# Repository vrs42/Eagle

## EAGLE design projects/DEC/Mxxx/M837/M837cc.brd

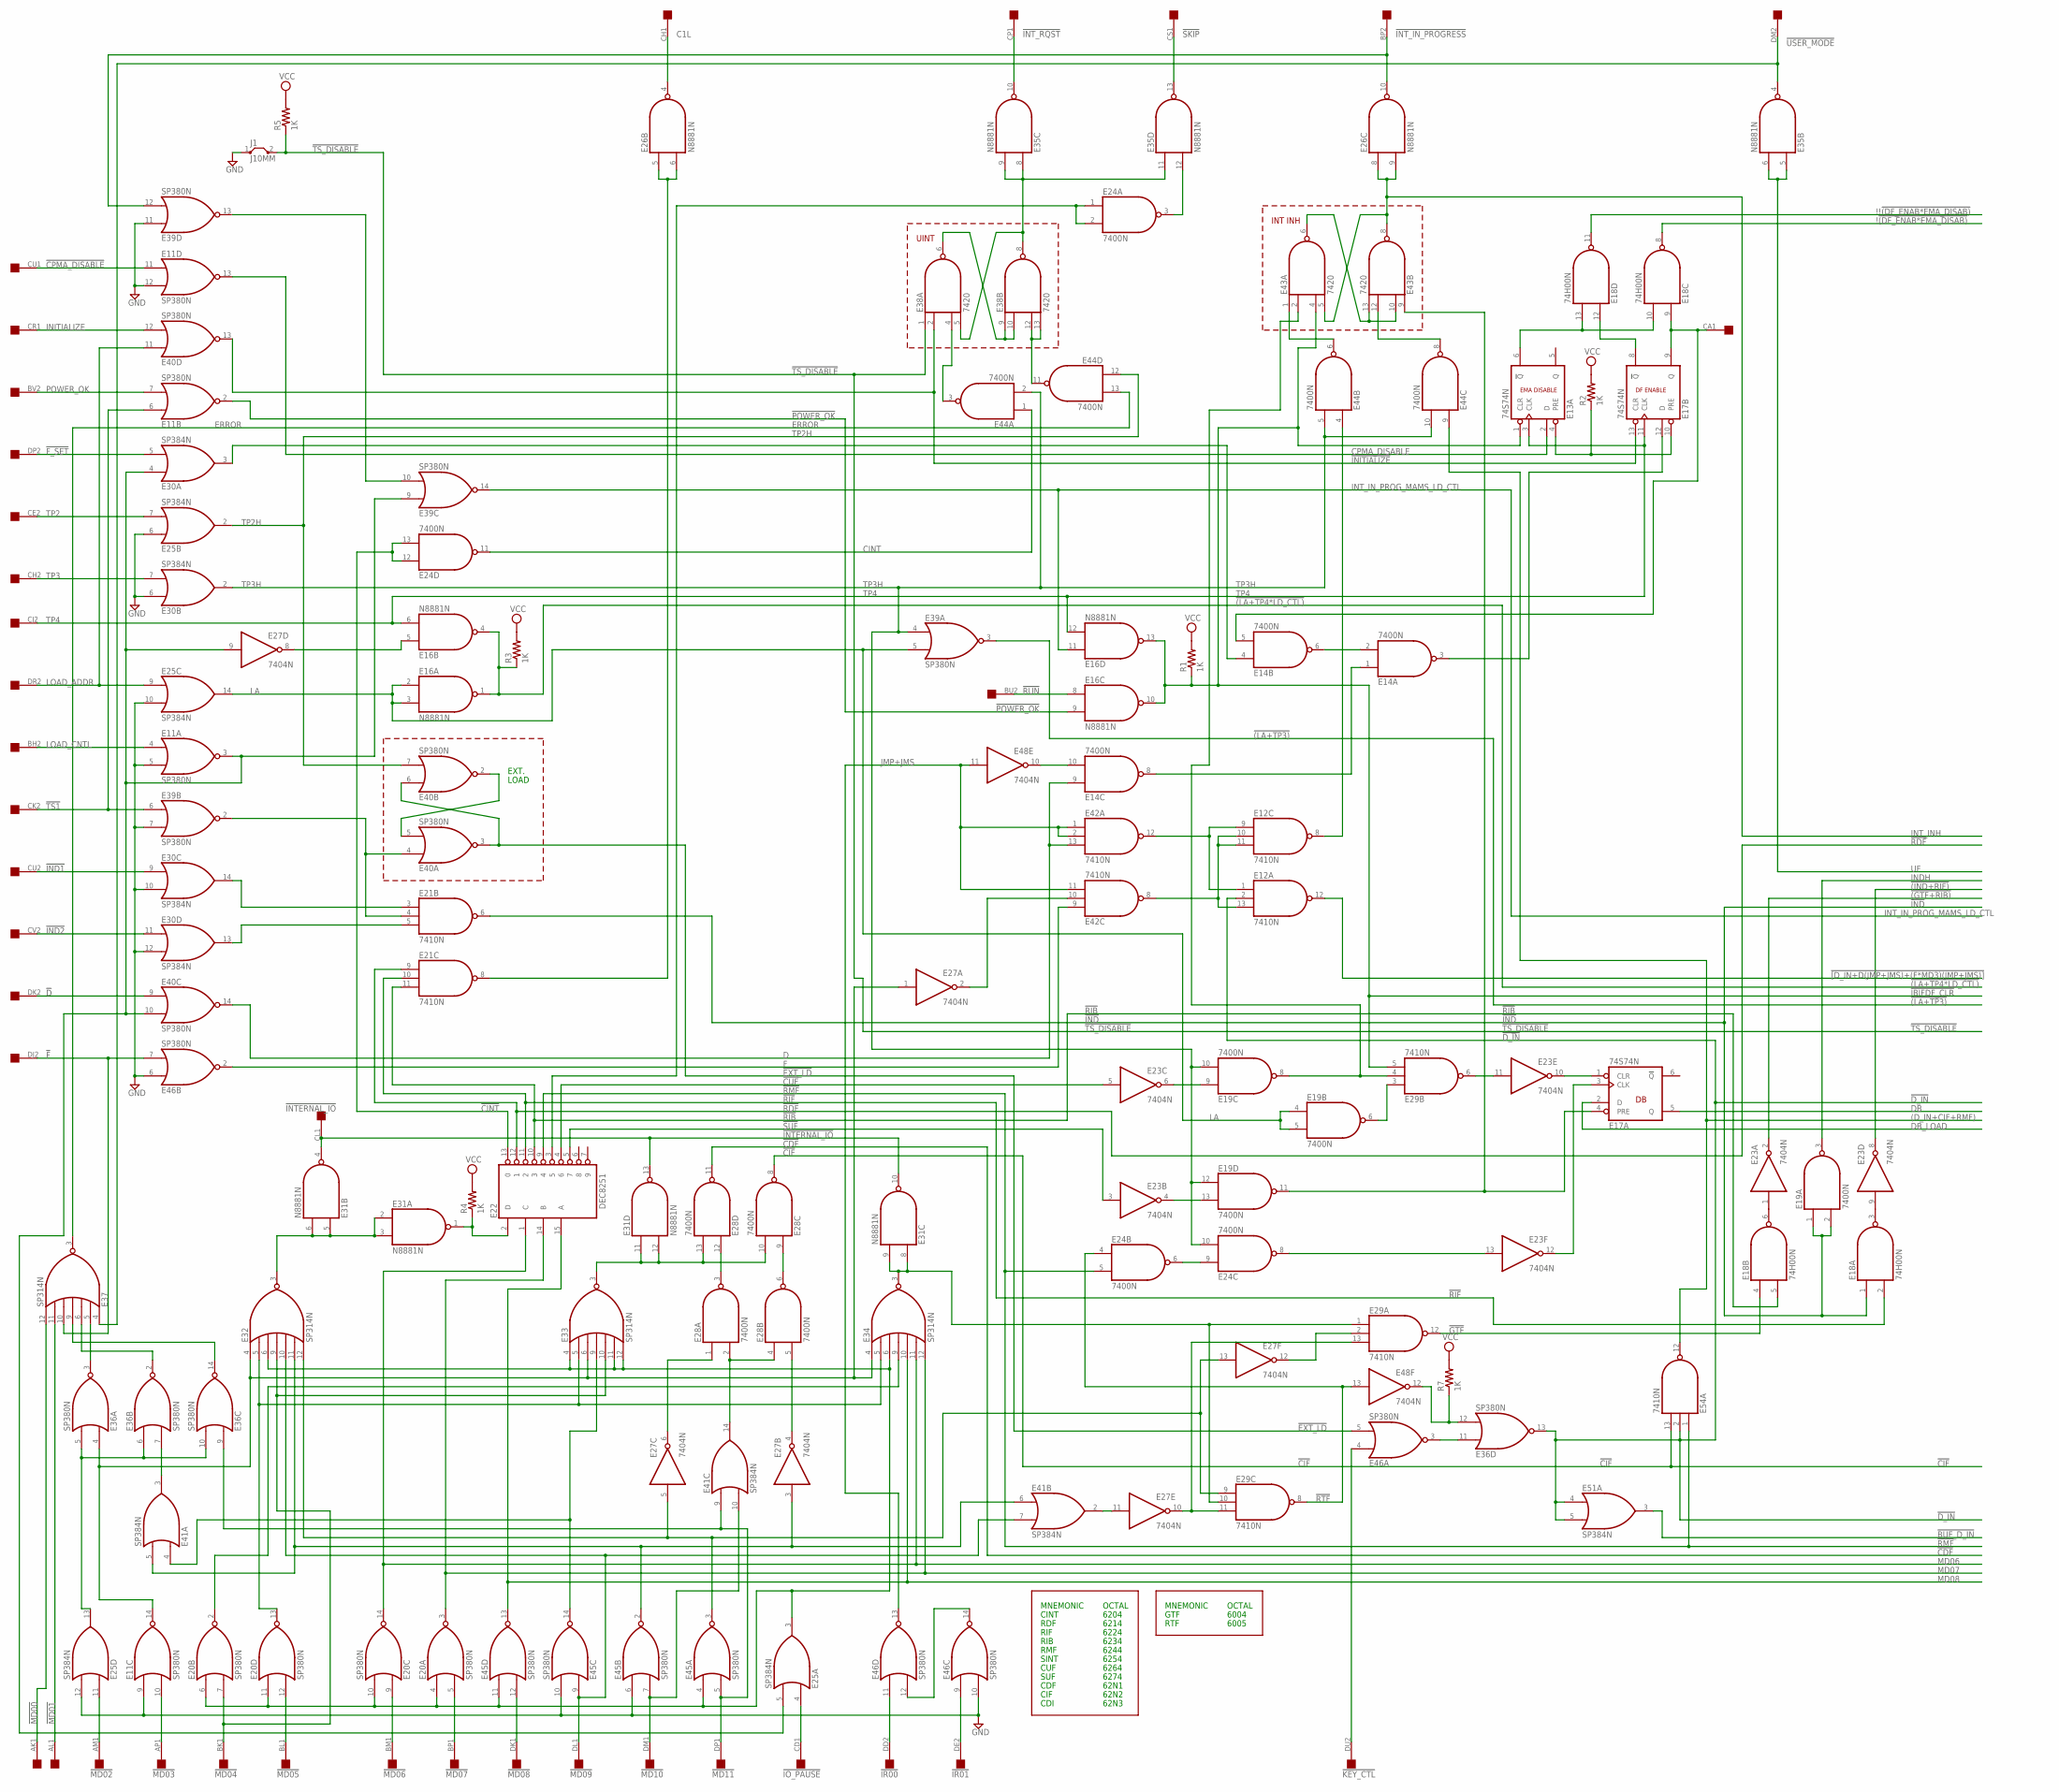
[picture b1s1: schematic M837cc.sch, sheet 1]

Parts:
E11, E20, E36, E39, E40, E45, E46: SP380N; DIL14
E12, E21, E29, E42, E54: 7410N; DIL14
E13, E17: 74S74N; DIL14
E14, E19, E24, E28, E44: 7400N; DIL14
E16, E26, E31, E35: N8881N; DIL14
E18: 74H00N; DIL14
E22: DEC8251; DIL16
E23, E27, E48: 7404N; DIL14
E25, E30, E41, E51: SP384N; DIL14
E32, E33, E34, E37: SP314N; DIL14
E38, E43: 7420; DIL14
EDGE: QUAD; EDGE-CON8
J1: J10MM; 10
R1, R2, R3, R4, R5, R7: 1K; 0207/10

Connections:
!(DF_ENAB*EMA_DISAB_L): E18.8 (O); also elsewhere on the board
!(DF_ENAB_L*EMA_DISAB_L): E18.11 (O); also elsewhere on the board
!(GTF+RIB): E23.2 (O); also elsewhere on the board
!(IND+RIF): E23.8 (O); also elsewhere on the board
!(LA+TP3): E39.3 (O); also elsewhere on the board
!(LA+TP4*LD_CTL): E16.1 (O), E16.4 (O), R3.1; also elsewhere on the board
!BMD02: E25.13 (O), E36.5 (I1), E36.6 (I0), E36.10 (I1)
!BUF_D_IN: E51.3 (O); also elsewhere on the board
!CDF: E28.11 (O); also elsewhere on the board
!CIF: E28.8 (O), E54.13 (I2); also elsewhere on the board
!CINT: E22.13 (0), E24.12 (I0), E24.13 (I1)
!CPMA_DISABLE: E11.11 (I0), EDGE.CU1
!CUF: E22.4 (6), E23.5 (I)
!D: E40.9 (I0), EDGE.DK2
!DF_ENABLE: E17.8 (!Q), E18.12 (I0)
!D_IN: E12.2 (I1), E36.13 (O), E51.4 (I0), E51.5 (I1), E54.2 (I1); also elsewhere on the board
!EMA_DISABLE: E13.6 (!Q), E18.10 (I1), E18.13 (I1)
!EXT_LD: E40.3 (O), E40.6 (I0), E46.5 (I1)
!F: E37.10 (I4), E46.7 (I1), EDGE.DJ2
!F_SET: E30.5 (I1), EDGE.DP2
!GTF: E18.4 (I0), E29.12 (O)
!IBIFDF_CLR: E13.1 (CLR), E16.10 (O), E16.13 (O), E29.5 (I2), E43.4 (I2), R1.1; also elsewhere on the board
!IND: E18.1 (I0), E19.1 (I0), E19.2 (I1), E21.6 (O); also elsewhere on the board
!IND1: E30.9 (I0), EDGE.CU2
!IND2: E30.11 (I0), EDGE.CV2
!INITIALIZE: E17.13 (CLR), E38.2 (I1), E40.13 (O)
!INTERNAL_IO: E31.4 (O), E31.10 (O), E31.13 (O), EDGE.CL1
!INT_IN_PROGRESS: E26.10 (O), E39.12 (I1), EDGE.BP2
!INT_RQST: E35.10 (O), EDGE.CP1
!IOT010XXX1XX: E22.2 (D), E31.1 (O), R4.1
!IO_PAUSE: E25.4 (I0), EDGE.CD1
!IR00: E46.11 (I0), EDGE.DD2
!IR01: E46.9 (I0), EDGE.DE2
!KEY_CTL: E46.4 (I0), EDGE.DU2
!LOAD_CNTL: E11.3 (O), E25.5 (I1), E27.9 (I), E30.4 (I0), E39.9 (I0), E40.10 (I1)
!MD00: E37.12 (I6), EDGE.AK1
!MD01: E37.11 (I5), EDGE.AL1
!MD02: E25.11 (I0), EDGE.AM1
!MD03: E11.10 (I1), EDGE.AP1
!MD04: E20.7 (I1), E32.9 (I3), E33.10 (I4), EDGE.BK1
!MD05: E20.12 (I1), EDGE.BL1
!MD06: E20.9 (I0), EDGE.BM1
!MD07: E20.5 (I1), EDGE.BP1
!MD08: E45.12 (I1), EDGE.DK1
!MD09: E32.10 (I4), E41.7 (I1), E45.9 (I0), EDGE.DL1
!MD10: E41.10 (I1), E45.7 (I1), EDGE.DM1
!MD11: E36.9 (I0), E41.9 (I0), E45.5 (I1), EDGE.DP1
!POWER_OK: E11.2 (O), E16.9 (I1)
!RDF: E21.9 (I0), E22.12 (1); also elsewhere on the board
!RIB: E18.5 (I1), E21.11 (I2), E22.10 (3)
!RIF: E18.2 (I1), E21.10 (I1), E22.11 (2)
!RMF: E22.9 (4), E24.5 (I1), E54.1 (I0); also elsewhere on the board
!RTF: E24.4 (I0), E29.8 (O), E48.13 (I)
!RUN: E16.8 (I0), EDGE.BU2
!SINT: E22.3 (5), E24.1 (I0), E24.2 (I1)
!SKIP: E35.13 (O), EDGE.CS1
!SUF: E22.5 (7), E23.3 (I)
!TS1: E11.6 (I0), E39.6 (I0), EDGE.CK2
!TS_DISABLE: E38.1 (I0), J1.2, R5.1; also elsewhere on the board
!USER_MODE: E35.4 (O), E37.4 (I0), EDGE.DM2
![D_IN+D(JMP+JMS)+(F*MD3)(JMP+JMS)]: E12.12 (O); also elsewhere on the board
(D_IN+CIF+RMF): E44.9 (I0), E54.12 (O); also elsewhere on the board
C1L: E26.4 (O), EDGE.CH1
CINT: E24.11 (O), E44.1 (I0)
CPMA_DISABLE: E11.13 (O), E13.2 (D)
D: E14.9 (I0), E40.14 (O), E42.13 (I2)
DB: E17.5 (Q); also elsewhere on the board
DB_LOAD: E17.2 (D); also elsewhere on the board
DF_ENABLE: E14.5 (I1), E17.9 (Q), E18.9 (I0), EDGE.CA1
ERROR: E37.3 (O), E44.13 (I1)
F: E42.9 (I0), E46.2 (O)
GND: E11.1 (GND), E11.5 (I1), E11.9 (I0), E11.12 (I1), E12.7 (GND), E13.7 (GND), E14.7 (GND), E16.7 (GND), E17.7 (GND), E18.7 (GND), E19.7 (GND), E20.1 (GND), E21.7 (GND), E22.8 (GND), E23.7 (GND), E24.7 (GND), E25.1 (GND), E25.6 (I0), E25.10 (I1), E25.12 (I1), E26.7 (GND), E27.7 (GND), E28.7 (GND), E29.7 (GND), E30.1 (GND), E30.6 (I0), E30.10 (I1), E30.12 (I1), E31.7 (GND), E32.1 (GND), E33.1 (GND), E34.1 (GND), E35.7 (GND), E36.1 (GND), E37.1 (GND), E38.7 (GND), E39.1 (GND), E39.7 (I1), E39.11 (I0), E40.1 (GND), E41.1 (GND), E42.7 (GND), E43.7 (GND), E44.7 (GND), E45.1 (GND), E45.6 (I0), E45.10 (I1), E46.1 (GND), E46.6 (I0), E46.10 (I1), E48.7 (GND), E51.1 (GND), E54.7 (GND), J1.1; also elsewhere on the board
IND1L: E21.3 (I0), E30.14 (O)
IND2L: E21.5 (I2), E30.13 (O)
INDH: E19.3 (O); also elsewhere on the board
INITIALIZE: E40.12 (I1), EDGE.CR1
INT_INH: E26.8 (I0), E26.9 (I1), E43.5 (I3), E43.8 (O); also elsewhere on the board
INT_IN_PROGRESS: E39.10 (I1), E39.13 (O)
INT_IN_PROG_MAMS_LD_CTL: E16.11 (I0), E39.14 (O); also elsewhere on the board
IOT000000XXX: E29.1 (I0), E29.10 (I1), E31.8 (I0), E31.9 (I1), E34.3 (O)
IOT010XXX0XX: E28.10 (I1), E28.13 (I1), E31.11 (I0), E31.12 (I1), E33.3 (O)
IOT010XXX1XX: E31.2 (I0), E31.3 (I1), E31.5 (I0), E31.6 (I1), E32.3 (O)
IO_PAUSE: E20.4 (I0), E20.6 (I0), E20.10 (I1), E20.11 (I0), E25.3 (O), E32.6 (I2), E33.4 (I0), E33.11 (I5), E33.12 (I6), E34.6 (I2), E45.4 (I0), E45.11 (I0)
IR01: E46.12 (I1), E46.14 (O)
JMP+JMS: E42.1 (I0), E42.2 (I1), E42.11 (I2), E46.13 (O), E48.11 (I)
LA: E16.2 (I0), E16.3 (I1), E19.4 (I0), E19.5 (I1), E25.14 (O), E39.5 (I1)
LOAD_ADDR: E25.9 (I0), E40.11 (I0), EDGE.DR2
LOAD_CNTL: E11.4 (I0), EDGE.BH2
LOAD_CNTLH: E16.5 (I0), E27.8 (O)
MD03: E11.14 (O), E27.1 (I), E32.4 (I0), E33.6 (I2), E34.4 (I0), E36.4 (I0)
MD03L: E27.2 (O), E42.10 (I1)
MD04: E20.2 (O), E34.9 (I3)
MD05: E20.13 (O), E32.5 (I1), E33.5 (I1), E34.5 (I1)
MD06: E20.14 (O), E22.1 (C), E34.11 (I5); also elsewhere on the board
MD07: E20.3 (O), E22.14 (B), E34.12 (I6); also elsewhere on the board
MD08: E22.15 (A), E34.10 (I4), E45.13 (O); also elsewhere on the board
MD09: E33.9 (I3), E41.4 (I0), E45.14 (O)
MD10: E27.3 (I), E32.11 (I5), E41.5 (I1), E41.6 (I0), E45.2 (O)
MD11: E27.5 (I), E27.13 (I), E29.9 (I0), E32.12 (I6), E45.3 (O)
MYC1: E21.8 (O), E26.5 (I0), E26.6 (I1)
unnamed: E24.3 (O), E35.12 (I1)
unnamed: E27.10 (O), E29.11 (I2), E29.13 (I2)
unnamed: E36.3 (O), E37.5 (I1)
unnamed: E36.2 (O), E37.6 (I2)
unnamed: E36.14 (O), E37.9 (I3)
unnamed: E14.2 (I1), E14.6 (O)
unnamed: E38.4 (I2), E44.3 (O)
unnamed: E40.2 (O), E40.5 (I1)
unnamed: E27.11 (I), E41.2 (O)
unnamed: E38.12 (I2), E38.13 (I3), E44.11 (O)
unnamed: E38.6 (O), E38.9 (I0), E38.10 (I1)
unnamed: E23.13 (I), E24.8 (O)
unnamed: E43.6 (O), E43.10 (I1), E43.13 (I3)
unnamed: E14.1 (I0), E14.8 (O)
unnamed: E36.7 (I1), E41.3 (O)
unnamed: E17.3 (CLK), E23.12 (O)
unnamed: E14.10 (I1), E48.10 (O)
unnamed: E18.3 (O), E23.9 (I)
unnamed: E12.10 (I1), E12.11 (I2), E12.13 (I2), E42.8 (O)
unnamed: E13.4 (PRE), E17.10 (PRE), R2.1
unnamed: E14.4 (I0), E30.3 (O)
unnamed: E12.1 (I0), E12.9 (I0), E42.12 (O)
unnamed: E18.6 (O), E23.1 (I)
unnamed: E14.3 (O), E17.12 (D)
unnamed: E28.2 (I1), E28.4 (I0), E41.14 (O)
unnamed: E19.6 (O), E29.3 (I0)
unnamed: E19.8 (O), E29.4 (I1), E43.2 (I1)
unnamed: E28.3 (O), E28.12 (I0)
unnamed: E28.6 (O), E28.9 (I0)
unnamed: E27.6 (O), E28.1 (I0)
unnamed: E27.4 (O), E28.5 (I1)
unnamed: E24.6 (O), E24.9 (I0)
unnamed: E19.13 (I1), E23.4 (O)
unnamed: E19.9 (I0), E23.6 (O)
unnamed: E17.1 (CLR), E23.10 (O)
unnamed: E23.11 (I), E29.6 (O)
unnamed: E27.12 (O), E29.2 (I1)
unnamed: E36.11 (I0), E46.3 (O)
unnamed: E17.4 (PRE), E19.11 (O), E43.9 (I0)
unnamed: E12.8 (O), E44.4 (I0)
unnamed: E43.1 (I0), E44.6 (O)
unnamed: E43.12 (I2), E44.8 (O)
POWER_OK: E11.7 (I1), EDGE.BV2
RTF: E36.12 (I1), E48.12 (O), R7.1
TP2: E25.7 (I1), EDGE.CE2
TP2H: E25.2 (O), E40.7 (I1), E44.12 (I0)
TP3: E30.7 (I1), EDGE.CH2
TP3H: E19.10 (I1), E19.12 (I0), E24.10 (I1), E30.2 (O), E39.4 (I0), E44.2 (I1), E44.5 (I1), E44.10 (I1)
TP4: E13.3 (CLK), E16.6 (I1), E16.12 (I1), E17.11 (CLK), EDGE.CJ2
TS1: E21.4 (I1), E39.2 (O), E40.4 (I0)
UF: E35.5 (I0), E35.6 (I1); also elsewhere on the board
UINT: E35.8 (I0), E35.9 (I1), E35.11 (I0), E38.5 (I3), E38.8 (O)
VCC: E11.8 (VCC), E12.14 (VCC), E13.14 (VCC), E14.14 (VCC), E16.14 (VCC), E17.14 (VCC), E18.14 (VCC), E19.14 (VCC), E20.8 (VCC), E21.14 (VCC), E22.16 (VCC), E23.14 (VCC), E24.14 (VCC), E25.8 (VCC), E26.14 (VCC), E27.14 (VCC), E28.14 (VCC), E29.14 (VCC), E30.8 (VCC), E31.14 (VCC), E32.8 (VCC), E33.8 (VCC), E34.8 (VCC), E35.14 (VCC), E36.8 (VCC), E37.8 (VCC), E38.14 (VCC), E39.8 (VCC), E40.8 (VCC), E41.8 (VCC), E42.14 (VCC), E43.14 (VCC), E44.14 (VCC), E45.8 (VCC), E46.8 (VCC), E48.14 (VCC), E51.8 (VCC), E54.14 (VCC), R1.2, R2.2, R3.2, R4.2, R5.2, R7.2; also elsewhere on the board

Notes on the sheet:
OCTAL
MNEMONIC
CINT
RDF
RIF
RIB
RMF
SINT
CUF
SUF
CDF
CIF
CDI
6204
6214
6224
6234
6244
6254
6264
6274
62N1
62N2
62N3
GTF
RTF
6004
6005
EXT.
LOAD
UINT
INT INH
EMA DISABLE
DF ENABLE

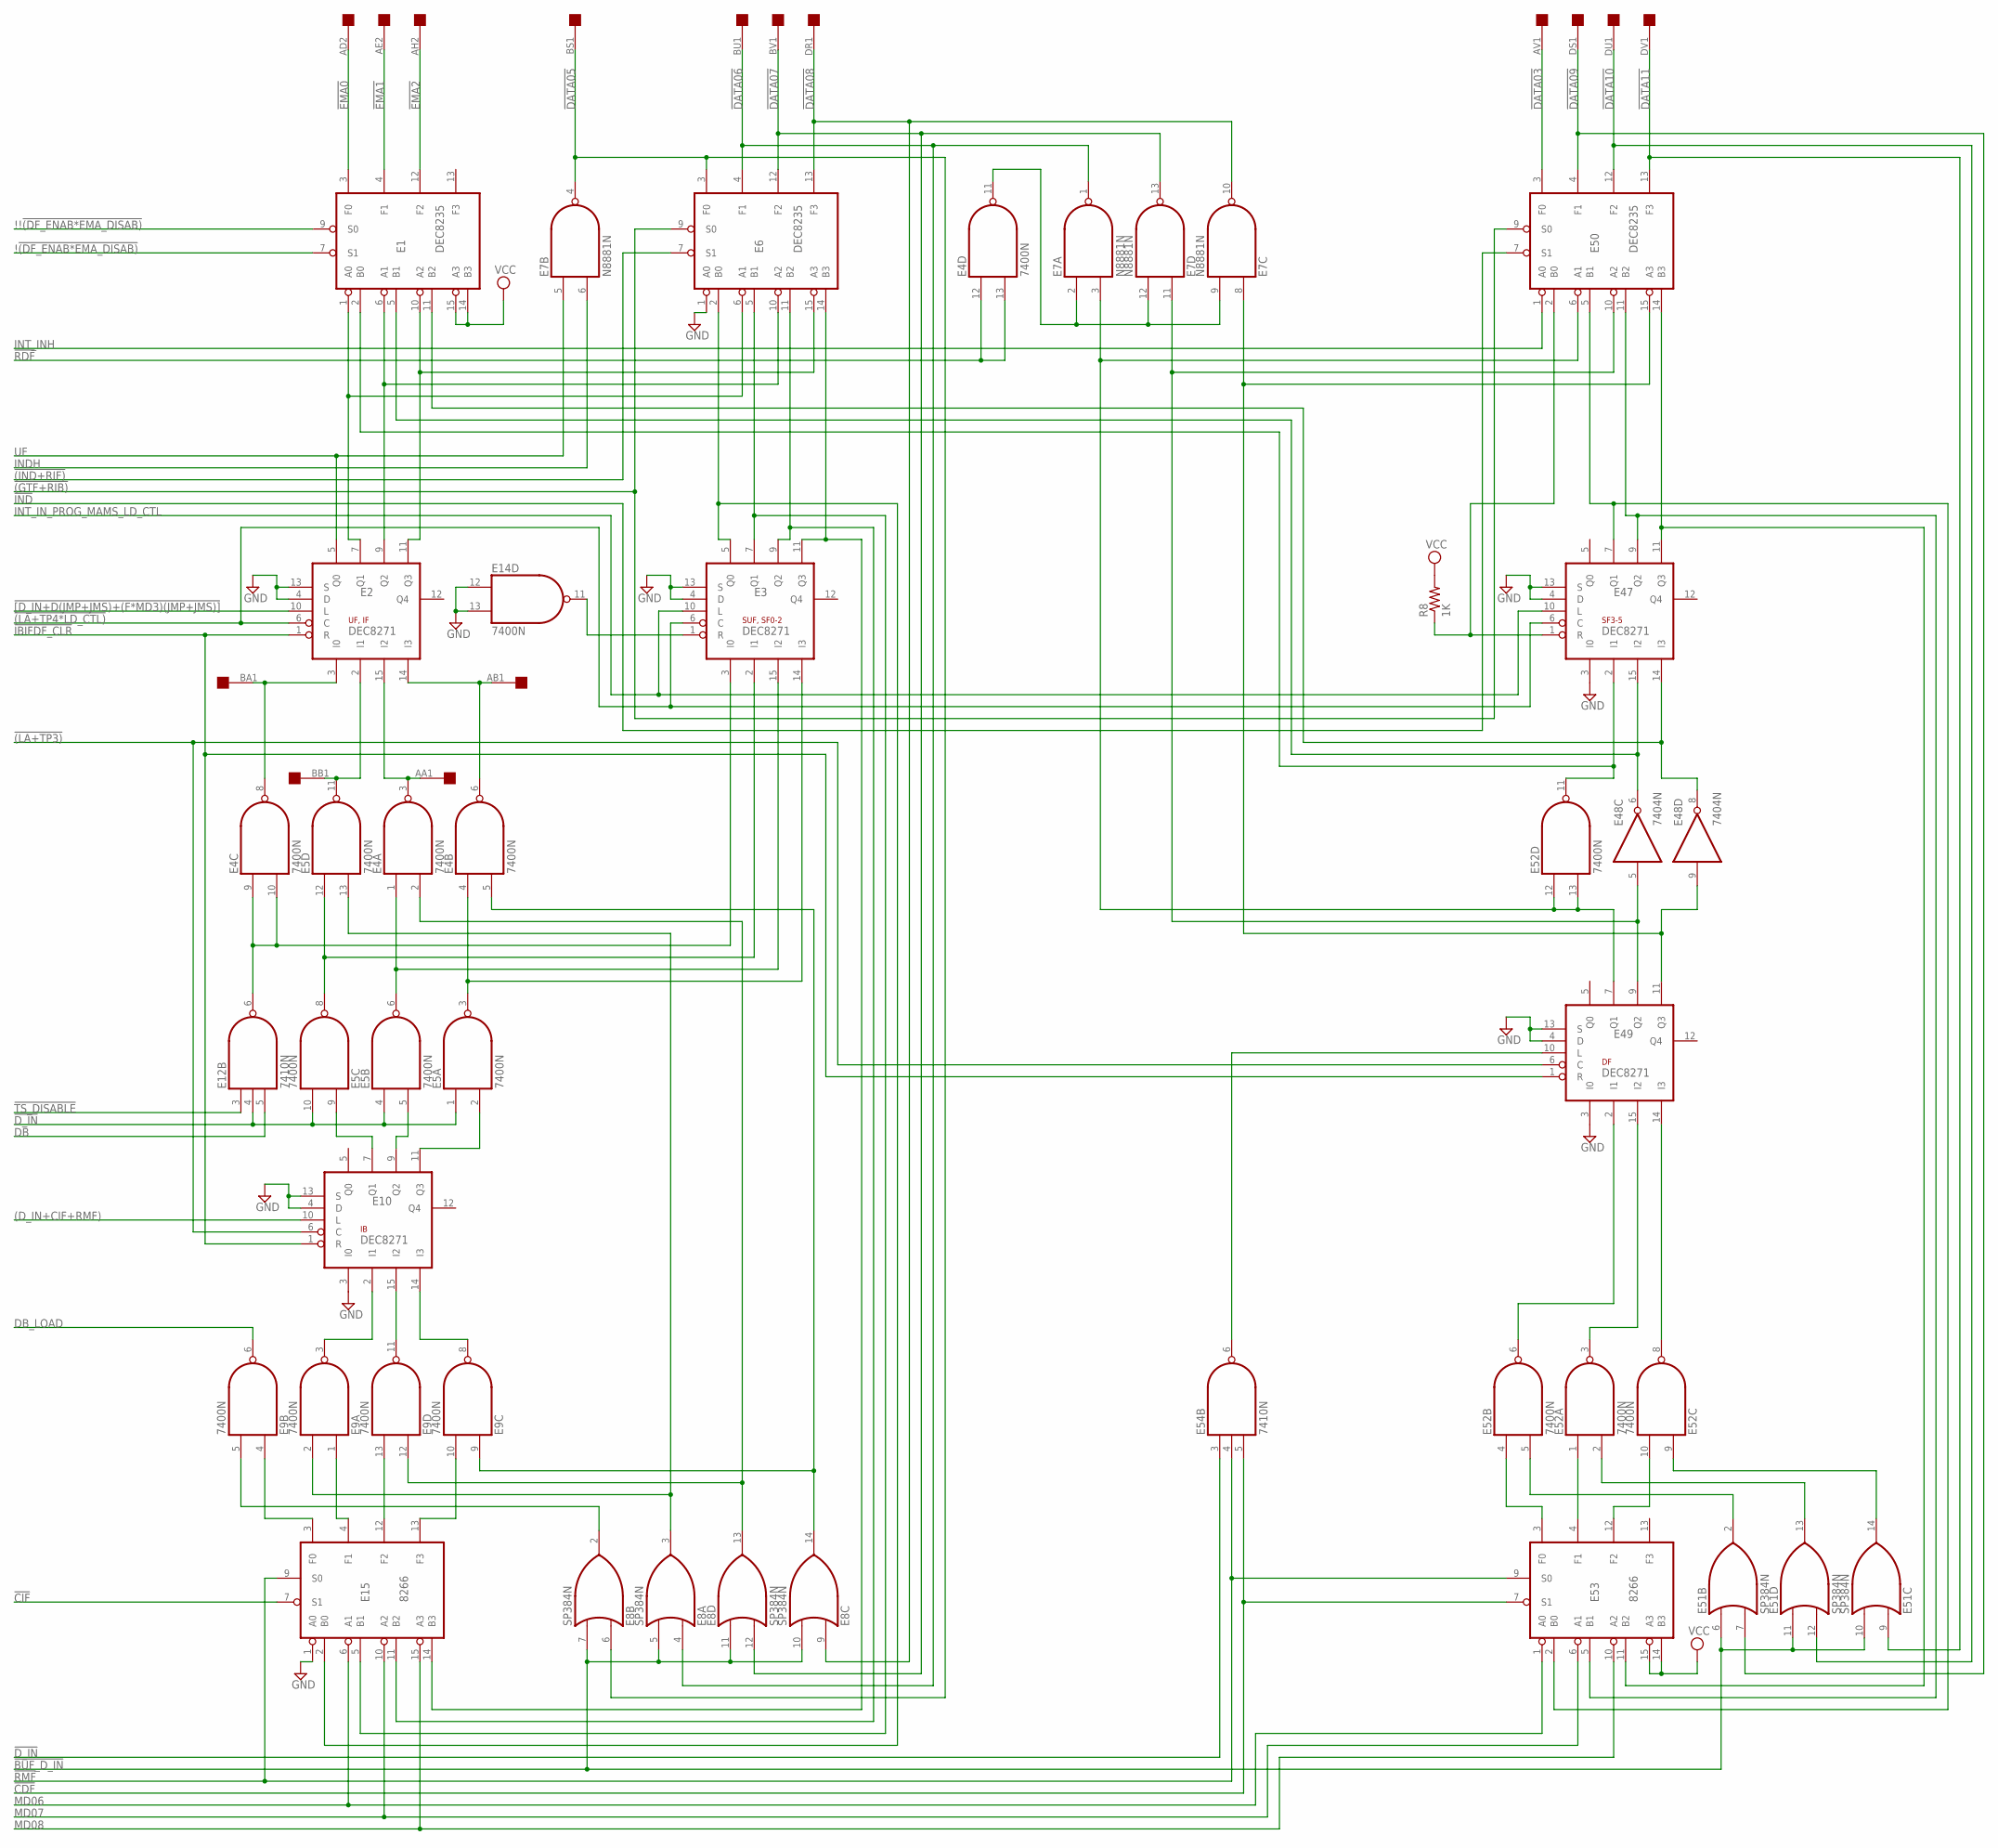
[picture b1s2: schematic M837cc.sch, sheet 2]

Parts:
E1, E6, E50: DEC8235; DIL16
E2, E3, E10, E47, E49: DEC8271; DIL16
E4, E5, E9, E14, E52: 7400N; DIL14
E7: N8881N; DIL14
E8, E51: SP384N; DIL14
E12, E54: 7410N; DIL14
E15, E53: 8266; DIL16
E48: 7404N; DIL14
EDGE: QUAD; EDGE-CON8
R8: 1K; 0207/10

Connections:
!(DF_ENAB*EMA_DISAB_L): E1.7 (S1); also elsewhere on the board
!(DF_ENAB_L*EMA_DISAB_L): E1.9 (S0); also elsewhere on the board
!(GTF+RIB): E6.9 (S0), E50.9 (S0); also elsewhere on the board
!(IND+RIF): E6.7 (S1); also elsewhere on the board
!(LA+TP3): E10.6 (C), E49.6 (C); also elsewhere on the board
!(LA+TP4*LD_CTL): E2.6 (C), E3.6 (C), E47.6 (C); also elsewhere on the board
!BUF_D_IN: E8.5 (I1), E8.7 (I1), E8.10 (I1), E8.11 (I0), E51.6 (I0), E51.10 (I1), E51.11 (I0); also elsewhere on the board
!CDF: E53.7 (S1), E54.5 (I2); also elsewhere on the board
!CIF: E15.7 (S1); also elsewhere on the board
!DATA03: E50.3 (F0), EDGE.AV1
!DATA05: E6.3 (F0), E7.4 (O), E8.6 (I0), EDGE.BS1
!DATA06: E6.4 (F1), E7.1 (O), E8.4 (I0), EDGE.BU1
!DATA07: E6.12 (F2), E7.13 (O), E8.12 (I1), EDGE.BV1
!DATA08: E6.13 (F3), E7.10 (O), E8.9 (I0), EDGE.DR1
!DATA09: E50.4 (F1), E51.7 (I1), EDGE.DS1
!DATA10: E50.12 (F2), E51.12 (I1), EDGE.DU1
!DATA11: E50.13 (F3), E51.9 (I0), EDGE.DV1
!D_IN: E5.1 (I0), E5.4 (I0), E5.10 (I1), E12.4 (I1), E54.3 (I0); also elsewhere on the board
!EMA0: E1.3 (F0), EDGE.AD2
!EMA1: E1.4 (F1), EDGE.AE2
!EMA2: E1.12 (F2), EDGE.AH2
!IBIFDF_CLR: E2.1 (R), E10.1 (R), E49.1 (R); also elsewhere on the board
!IND: E50.7 (S1); also elsewhere on the board
!RDF: E4.12 (I0), E4.13 (I1); also elsewhere on the board
!RMF: E15.9 (S0), E53.9 (S0), E54.4 (I1); also elsewhere on the board
!TS_DISABLE: E12.3 (I0); also elsewhere on the board
![D_IN+D(JMP+JMS)+(F*MD3)(JMP+JMS)]: E2.10 (L); also elsewhere on the board
(D_IN+CIF+RMF): E10.10 (L); also elsewhere on the board
DB: E12.5 (I2); also elsewhere on the board
DB_LOAD: E9.6 (O); also elsewhere on the board
DF0: E7.3 (I1), E49.7 (Q1), E50.6 (A1), E52.12 (I0), E52.13 (I1)
DF1: E7.11 (I0), E48.5 (I), E49.9 (Q2), E50.10 (A2)
DF2: E7.8 (I0), E48.9 (I), E49.11 (Q3), E50.15 (A3)
GND: E1.8 (GND), E2.4 (D), E2.8 (GND), E2.13 (S), E3.4 (D), E3.8 (GND), E3.13 (S), E4.7 (GND), E5.7 (GND), E6.1 (A0), E6.8 (GND), E7.7 (GND), E8.1 (GND), E9.7 (GND), E10.3 (I0), E10.4 (D), E10.8 (GND), E10.13 (S), E12.7 (GND), E14.7 (GND), E14.12 (I0), E14.13 (I1), E15.1 (A0), E15.8 (GND), E47.3 (I0), E47.4 (D), E47.8 (GND), E47.13 (S), E48.7 (GND), E49.3 (I0), E49.4 (D), E49.8 (GND), E49.13 (S), E50.8 (GND), E51.1 (GND), E52.7 (GND), E53.8 (GND), E54.7 (GND); also elsewhere on the board
IB0: E5.9 (I0), E10.7 (Q1)
IB1: E5.5 (I1), E10.9 (Q2)
IB2: E5.2 (I1), E10.11 (Q3)
IF0: E1.1 (A0), E2.7 (Q1), E6.6 (A1)
IF1: E1.6 (A1), E2.9 (Q2), E6.10 (A2)
IF2: E1.10 (A2), E2.11 (Q3), E6.15 (A3)
INDH: E7.6 (I1); also elsewhere on the board
INT_INH: E50.1 (A0); also elsewhere on the board
INT_IN_PROG_MAMS_LD_CTL: E3.10 (L), E47.10 (L); also elsewhere on the board
MD06: E15.6 (A1), E53.1 (A0); also elsewhere on the board
MD07: E15.10 (A2), E53.6 (A1); also elsewhere on the board
MD08: E15.15 (A3), E53.10 (A2); also elsewhere on the board
unnamed: E9.4 (I0), E15.3 (F0)
unnamed: E9.1 (I0), E15.4 (F1)
unnamed: E9.13 (I1), E15.12 (F2)
unnamed: E9.10 (I1), E15.13 (F3)
unnamed: E8.2 (O), E9.5 (I1)
unnamed: E5.13 (I1), E8.3 (O), E9.2 (I1)
unnamed: E4.2 (I1), E8.13 (O), E9.12 (I0)
unnamed: E4.5 (I1), E8.14 (O), E9.9 (I0)
unnamed: E9.11 (O), E10.15 (I2)
unnamed: E9.3 (O), E10.2 (I1)
unnamed: E9.8 (O), E10.14 (I3)
unnamed: E3.14 (I3), E4.4 (I0), E5.3 (O)
unnamed: E3.15 (I2), E4.1 (I0), E5.6 (O)
unnamed: E3.2 (I1), E5.8 (O), E5.12 (I0)
unnamed: E3.3 (I0), E4.9 (I0), E4.10 (I1), E12.6 (O)
unnamed: E1.11 (B2), E47.14 (I3), E48.8 (O)
unnamed: E1.5 (B1), E47.15 (I2), E48.6 (O)
unnamed: E1.2 (B0), E47.2 (I1), E52.11 (O)
unnamed: E49.10 (L), E54.6 (O)
unnamed: E51.2 (O), E52.5 (I1)
unnamed: E51.13 (O), E52.2 (I1)
unnamed: E51.14 (O), E52.9 (I0)
unnamed: E52.1 (I0), E53.4 (F1)
unnamed: E52.10 (I1), E53.12 (F2)
unnamed: E3.1 (R), E14.11 (O)
unnamed: E52.4 (I0), E53.3 (F0)
unnamed: E49.14 (I3), E52.8 (O)
unnamed: E49.15 (I2), E52.3 (O)
unnamed: E49.2 (I1), E52.6 (O)
unnamed: E47.1 (R), E50.2 (B0), R8.1
RDF: E4.11 (O), E7.2 (I0), E7.9 (I1), E7.12 (I1)
SF0_L: E3.7 (Q1), E6.5 (B1), E15.5 (B1)
SF1_L: E3.9 (Q2), E6.11 (B2), E15.11 (B2)
SF2_L: E3.11 (Q3), E6.14 (B3), E15.14 (B3)
SF3_L: E47.7 (Q1), E50.5 (B1), E53.2 (B0)
SF4_L: E47.9 (Q2), E50.11 (B2), E53.5 (B1)
SF5_L: E47.11 (Q3), E50.14 (B3), E53.11 (B2)
SUF_L: E3.5 (Q0), E6.2 (B0), E15.2 (B0)
TP_AA1: E2.15 (I2), E4.3 (O), EDGE.AA1
TP_AB1: E2.14 (I3), E4.6 (O), EDGE.AB1
TP_BA1: E2.3 (I0), E4.8 (O), EDGE.BA1
TP_BB1: E2.2 (I1), E5.11 (O), EDGE.BB1
UF: E2.5 (Q0), E7.5 (I0); also elsewhere on the board
VCC: E1.14 (B3), E1.15 (A3), E1.16 (VCC), E2.16 (VCC), E3.16 (VCC), E4.14 (VCC), E5.14 (VCC), E6.16 (VCC), E7.14 (VCC), E8.8 (VCC), E9.14 (VCC), E10.16 (VCC), E12.14 (VCC), E14.14 (VCC), E15.16 (VCC), E47.16 (VCC), E48.14 (VCC), E49.16 (VCC), E50.16 (VCC), E51.8 (VCC), E52.14 (VCC), E53.14 (B3), E53.15 (A3), E53.16 (VCC), E54.14 (VCC), R8.2; also elsewhere on the board

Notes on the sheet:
SUF, SF0-2
UF, IF
SF3-5

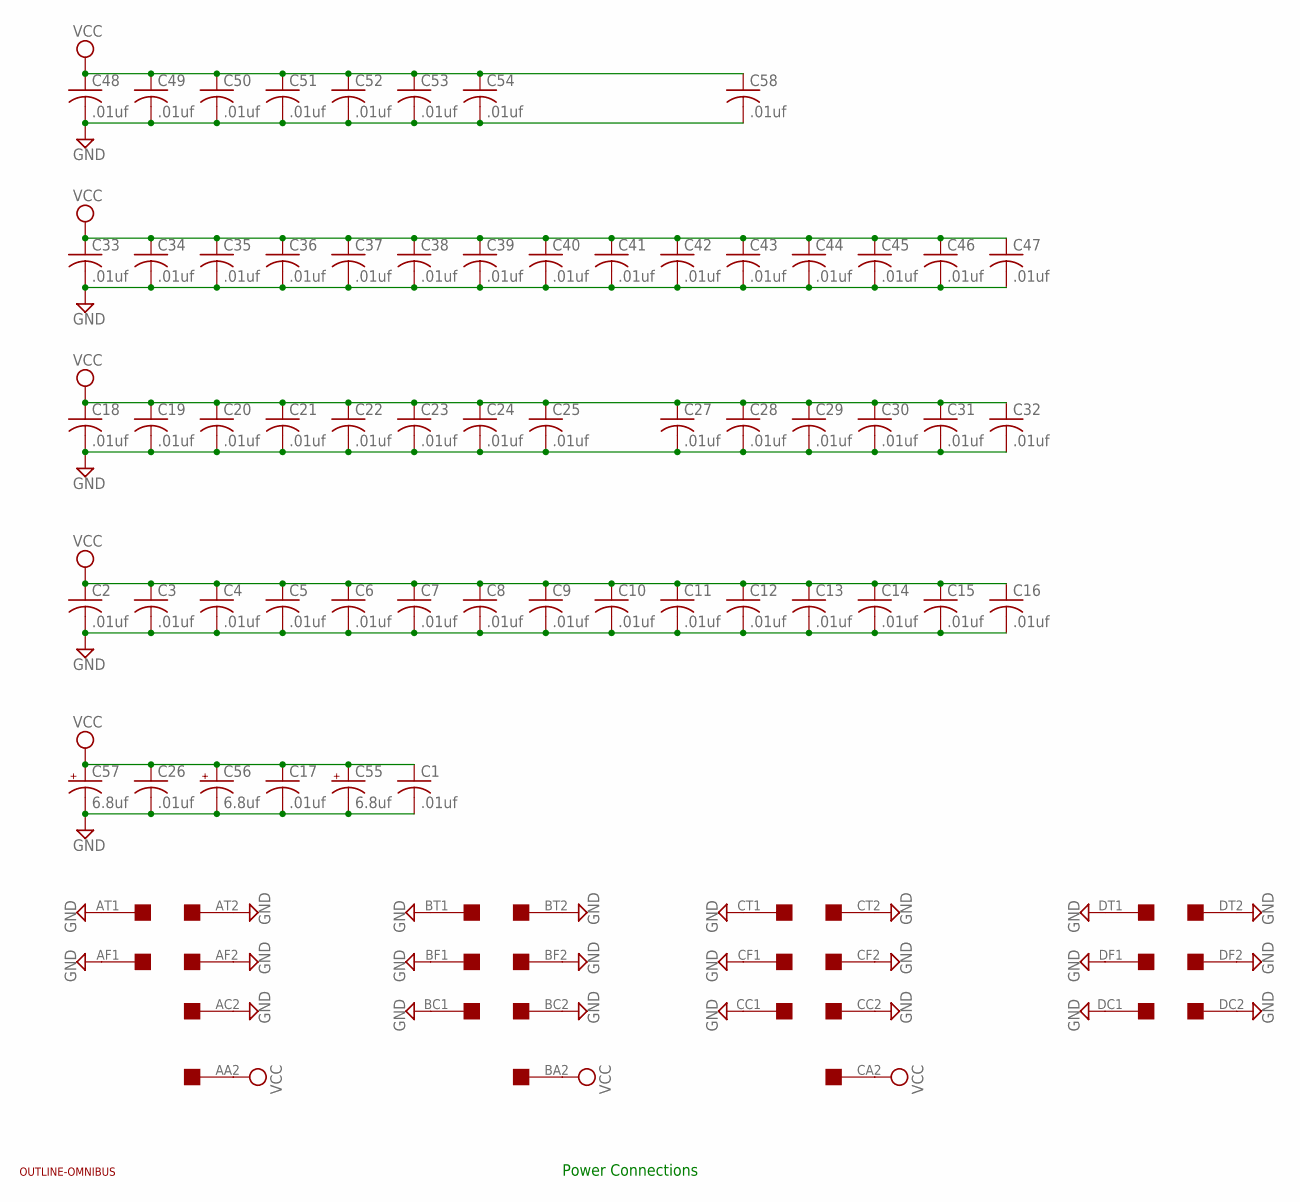
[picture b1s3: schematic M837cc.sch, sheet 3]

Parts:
C1, C2, C3, C4, C5, C6, C7, C8, C9, C10, C11, C12, C13, C14, C15, C16, C17, C18, C19, C20, C21, C22, C23, C24, C25, C26, C27, C28, C29, C30, C31, C32, C33, C34, C35, C36, C37, C38, C39, C40, C41, C42, C43, C44, C45, C46, C47, C48, C49, C50, C51, C52, C53, C54, C58: .01uf; C050-025X075
C55, C56, C57: 6.8uf; E22-6
EDGE: QUAD; EDGE-CON8
U$1: OUTLINE-OMNIBUS; OMNIBUS

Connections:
GND: C1.2, C2.2, C3.2, C4.2, C5.2, C6.2, C7.2, C8.2, C9.2, C10.2, C11.2, C12.2, C13.2, C14.2, C15.2, C16.2, C17.2, C18.2, C19.2, C20.2, C21.2, C22.2, C23.2, C24.2, C25.2, C26.2, C27.2, C28.2, C29.2, C30.2, C31.2, C32.2, C33.2, C34.2, C35.2, C36.2, C37.2, C38.2, C39.2, C40.2, C41.2, C42.2, C43.2, C44.2, C45.2, C46.2, C47.2, C48.2, C49.2, C50.2, C51.2, C52.2, C53.2, C54.2, C55.-, C56.-, C57.-, C58.2, EDGE.AC2, EDGE.AF1, EDGE.AF2, EDGE.AT1, EDGE.AT2, EDGE.BC1, EDGE.BC2, EDGE.BF1, EDGE.BF2, EDGE.BT1, EDGE.BT2, EDGE.CC1, EDGE.CC2, EDGE.CF1, EDGE.CF2, EDGE.CT1, EDGE.CT2, EDGE.DC1, EDGE.DC2, EDGE.DF1, EDGE.DF2, EDGE.DT1, EDGE.DT2; also elsewhere on the board
VCC: C1.1, C2.1, C3.1, C4.1, C5.1, C6.1, C7.1, C8.1, C9.1, C10.1, C11.1, C12.1, C13.1, C14.1, C15.1, C16.1, C17.1, C18.1, C19.1, C20.1, C21.1, C22.1, C23.1, C24.1, C25.1, C26.1, C27.1, C28.1, C29.1, C30.1, C31.1, C32.1, C33.1, C34.1, C35.1, C36.1, C37.1, C38.1, C39.1, C40.1, C41.1, C42.1, C43.1, C44.1, C45.1, C46.1, C47.1, C48.1, C49.1, C50.1, C51.1, C52.1, C53.1, C54.1, C55.+, C56.+, C57.+, C58.1, EDGE.AA2, EDGE.BA2, EDGE.CA2; also elsewhere on the board

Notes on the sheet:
Power Connections

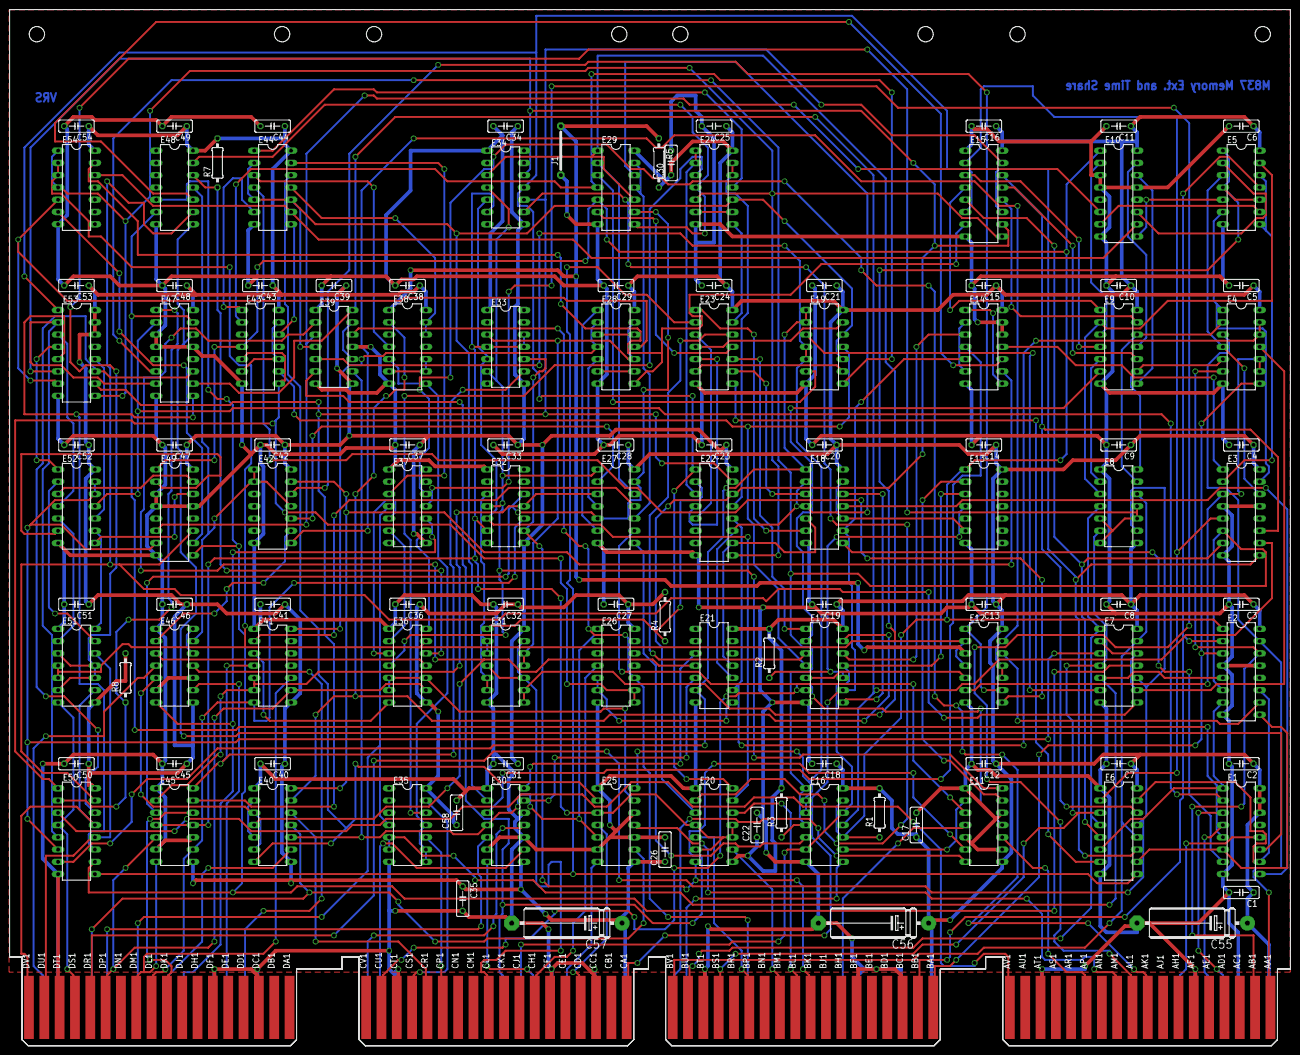
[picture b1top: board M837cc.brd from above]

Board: 2 copper layers, 265.3 x 214.6 mm, 122 parts (0 on the bottom side), 215 nets.

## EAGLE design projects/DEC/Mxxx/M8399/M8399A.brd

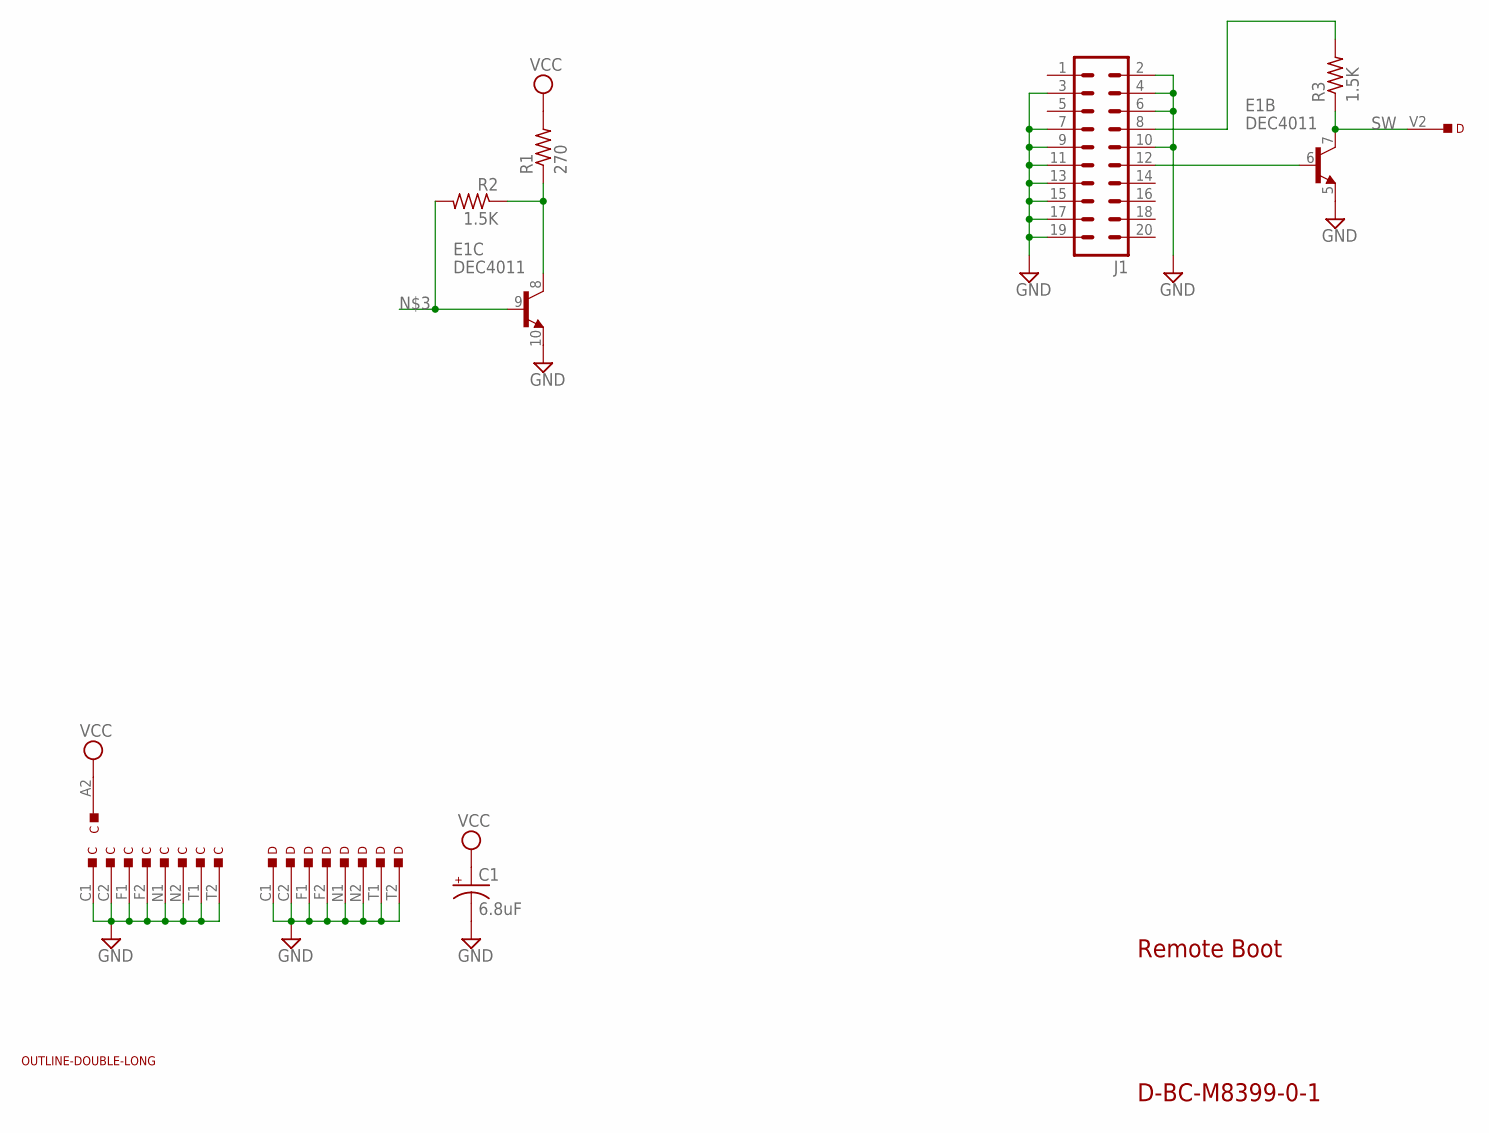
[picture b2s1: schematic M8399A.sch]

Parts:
C: EDGE-TOP; EDGE-CON2
C1: 6.8uF; E12-8
D: EDGE-TOP; EDGE-CON2
E1: DEC4011; DIL14
J1: 20H
R1: 270; 0207/10
R2, R3: 1.5K; 0207/10
U$1: OUTLINE-DOUBLE-LONG; DOUBLE-LONG

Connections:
GND: C.C1, C.C2, C.F1, C.F2, C.N1, C.N2, C.T1, C.T2, C1.-, D.C1, D.C2, D.F1, D.F2, D.N1, D.N2, D.T1, D.T2, E1.5 (E), E1.10 (E), J1.2, J1.3, J1.4, J1.6, J1.7, J1.9, J1.10, J1.11, J1.13, J1.15, J1.17, J1.19
unnamed: E1.8 (C), R1.1, R2.1
unnamed: J1.8, R3.2
unnamed: E1.9 (B), R2.2
unnamed: E1.6 (B), J1.12
SW: D.V2, E1.7 (C), R3.1
VCC: C.A2, C1.+, R1.2

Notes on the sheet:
Remote Boot
D-BC-M8399-0-1
